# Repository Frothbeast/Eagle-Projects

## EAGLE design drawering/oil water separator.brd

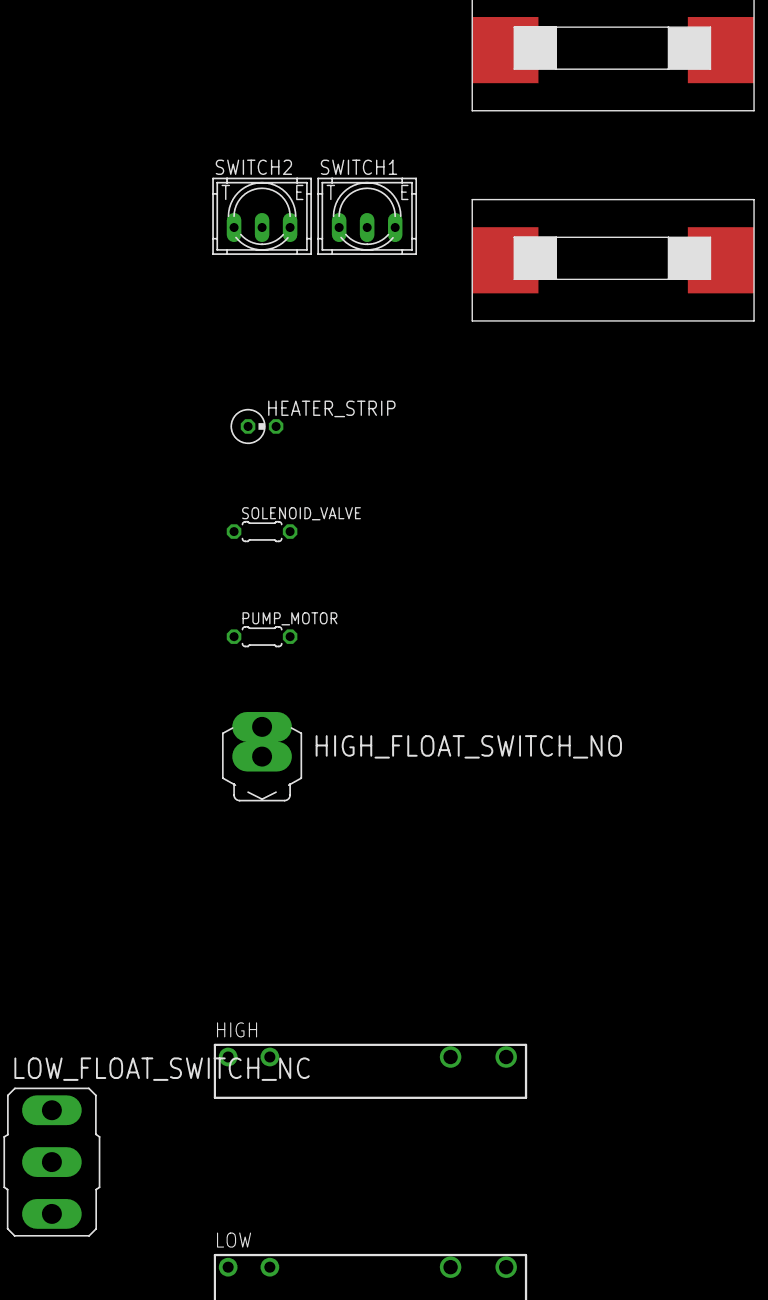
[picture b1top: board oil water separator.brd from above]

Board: 2 copper layers, 11 parts (0 on the bottom side), 9 nets, no tracks yet.

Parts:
HEATER_STRIP: 0309V
HIGH: APF30212A
HIGH_FLOAT_SWITCH_NO: MS243
LOW: APF30212A
LOW_FLOAT_SWITCH_NC: M9040P
PUMP_MOTOR: 0204/5
SOLENOID_VALVE: 0204/5
SWITCH1: toggle; 9077-1
SWITCH2: Momentary; 9077-1
U$1, U$2: FUSE(SM); FUSE

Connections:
unnamed: HEATER_STRIP.2, LOW.NO, PUMP_MOTOR.2, SOLENOID_VALVE.2
unnamed: U$1.P$1, U$2.P$1
unnamed: HIGH.1, HIGH_FLOAT_SWITCH_NO.1, LOW.2
unnamed: SWITCH1.2, SWITCH2.2, U$1.P$2
unnamed: HEATER_STRIP.1, SWITCH1.1
unnamed: HIGH.2, HIGH.COM, HIGH_FLOAT_SWITCH_NO.2
unnamed: LOW.1, LOW_FLOAT_SWITCH_NC.2, U$2.P$2
unnamed: HIGH.NO, PUMP_MOTOR.1, SOLENOID_VALVE.1, SWITCH2.3
unnamed: LOW.COM, LOW_FLOAT_SWITCH_NC.1
